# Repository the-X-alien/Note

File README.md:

# Note
An open source speaker for all your music needs. Completed with dual speakers and bluetooth compatibility, this speaker is a great deal at just manufacturing price. Have the fun and get the brag rights of building your own speaker and get to keep a sweet final product. I made this project because I saw a picture of a speaker on the starter projects section but there was no guide on how to make a speaker, so I decided I make one myself.

My Assembled Project

My PCB

BOM:
| Quantity | Designation and Description                                          | Price |
|----------|----------------------------------------------------------------------|-------|
| 1        | LD1117V33 (3.3V voltage regulator)                                   | $6.53 |
| 1        | 2 40 mm Speaker                                                      | $7.86 |
| 1        | TP4056 (Charger for receiving power and sending it to the battery)   | $6.00 |
| 1        | ESP32-WROOM-32                                                       | $14.00|
| 1        | Connector for 3.7v battery                                           | $6.00 |
| 1        | 3.7v Battery                                                         | $9.00 |
| 1        | PAM8403 (Audio Amplifier)                                            | $6.00 |
| 1        | MT3608 (Boost Converter to 5V)                                       | $6.00 |
| 1        | Copper wire for speakers and bad footprints                          | $8.00 |
| 1        | PCB                                                                  | $25.00|
|          | **Total:**                                                           | **~$94.39**+ Tax = **103.24**|

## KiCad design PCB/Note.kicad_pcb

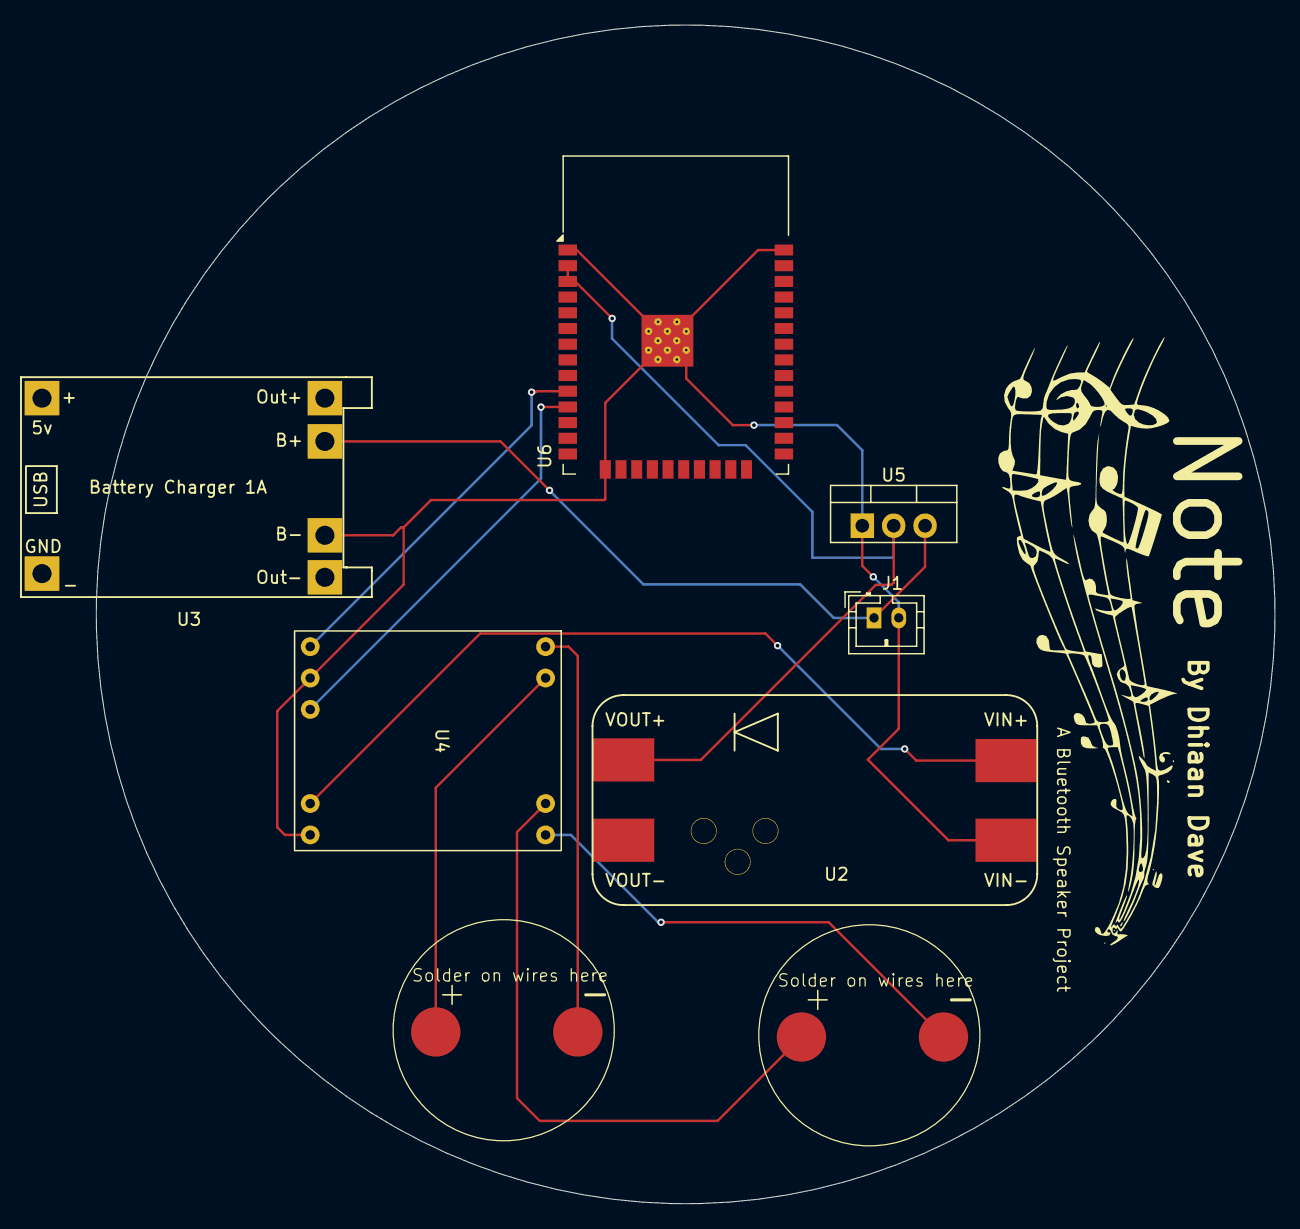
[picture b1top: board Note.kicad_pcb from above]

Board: 2 copper layers, 95.4 x 95.4 mm, 8 parts (0 on the bottom side), 10 nets.

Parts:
J1: Conn_01x02; JST_PH_B2B-PH-K_02x2.00mm_Straight
LS1, LS2: Speaker; SPKR
U2: MT3608; MT3608_module_SMT
U3: TP4056-18650
U4: pam8403
U5: LD1117V33; TO-220-3_Vertical
U6: ESP32-WROOM-32

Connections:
3.3V: U2.4 (EN), U5.2 (VO), U6.2 (VDD), U6.3 (EN)
GND: J1.2, U2.2 (GND), U3.6 (B-), U4.2 (T), U4.5 (GND), U5.1 (GND), U6.1 (GND), U6.15 (GND), U6.38 (GND), U6.39 (GND)
GPIO25: U4.1 (L), U6.10 (IO25)
GPIO26: U4.3 (R), U6.11 (IO26)
L+: LS1.1, U4.8 (L+)
L-: LS1.2, U4.9 (L-)
R+: LS2.1, U4.7 (R+)
R-: LS2.2, U4.6 (R-)
VBAT: J1.1, U3.5 (B+), U5.3 (VI)
VBUS: U2.1 (SW), U4.4 (vin)

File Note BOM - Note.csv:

Id,Designator,Footprint,Quantity,Designation and Description,Supplier and ref,Price
1,U5,TO-220-3_Vertical,1,LD1117V33 (3.3V voltage regulator),https://www.adafruit.com/product/2165?srsltid=AfmBOorJFm1Aak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,$6.53
2,"LS2,LS1",SPKR,2,2 40 mm Speaker,https://www.amazon.com/Gikfun-Speaker-Stereo-Loudspeaker-Ard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,$7.86
3,U3,TP4056-18650,1,TP4056 (Charger for receving power and sending it to the battery),https://www.amazon.com/HiLetgo-Lithium-Charging-Protection-F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,$6
4,U6,ESP32-WROOM-32,1,ESP32-WROOM-32,https://www.amazon.com/Hosyond-ESP-WROOM-32-Development-Micr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,$14
5,J1,JST_PH_B2B-PH-K_02x2.00mm_Straight,1,Connector for 3.7v battery,https://www.amazon.com/CQRobot-Pieces-Connector-Housing-Adap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,$6
,,,1,3.7v Battery,https://www.amazon.com/Battery-Rechargeable-Lithium-Polymer-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,$9
6,U4,pam8403,1,pam8403 (Audio Amplifier),https://www.amazon.com/HiLetgo%C2%AE-PAM8403-Digital-Amplifi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,$6
7,U2,MT3608_module_SMT,1,MT3608 (Boost Converter to 5V),https://www.amazon.com/MT3608-Converter-Supply-Module-2V-24V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,$6
,,,1,Copper wire so speakers can move and for bad footprints,https://www.amazon.com/Enameled-Winding-Temperature-Transfor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,$8
,,,1,PCB,PCB Way or JLCPCB,$25
,,,,,Total:,$94.39

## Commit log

2025-06-21 Update LICENSE
2025-06-27 Create temp1
2025-06-27 Create temp2
2025-06-27 Create temp3
2025-07-06 Added various timestamps
